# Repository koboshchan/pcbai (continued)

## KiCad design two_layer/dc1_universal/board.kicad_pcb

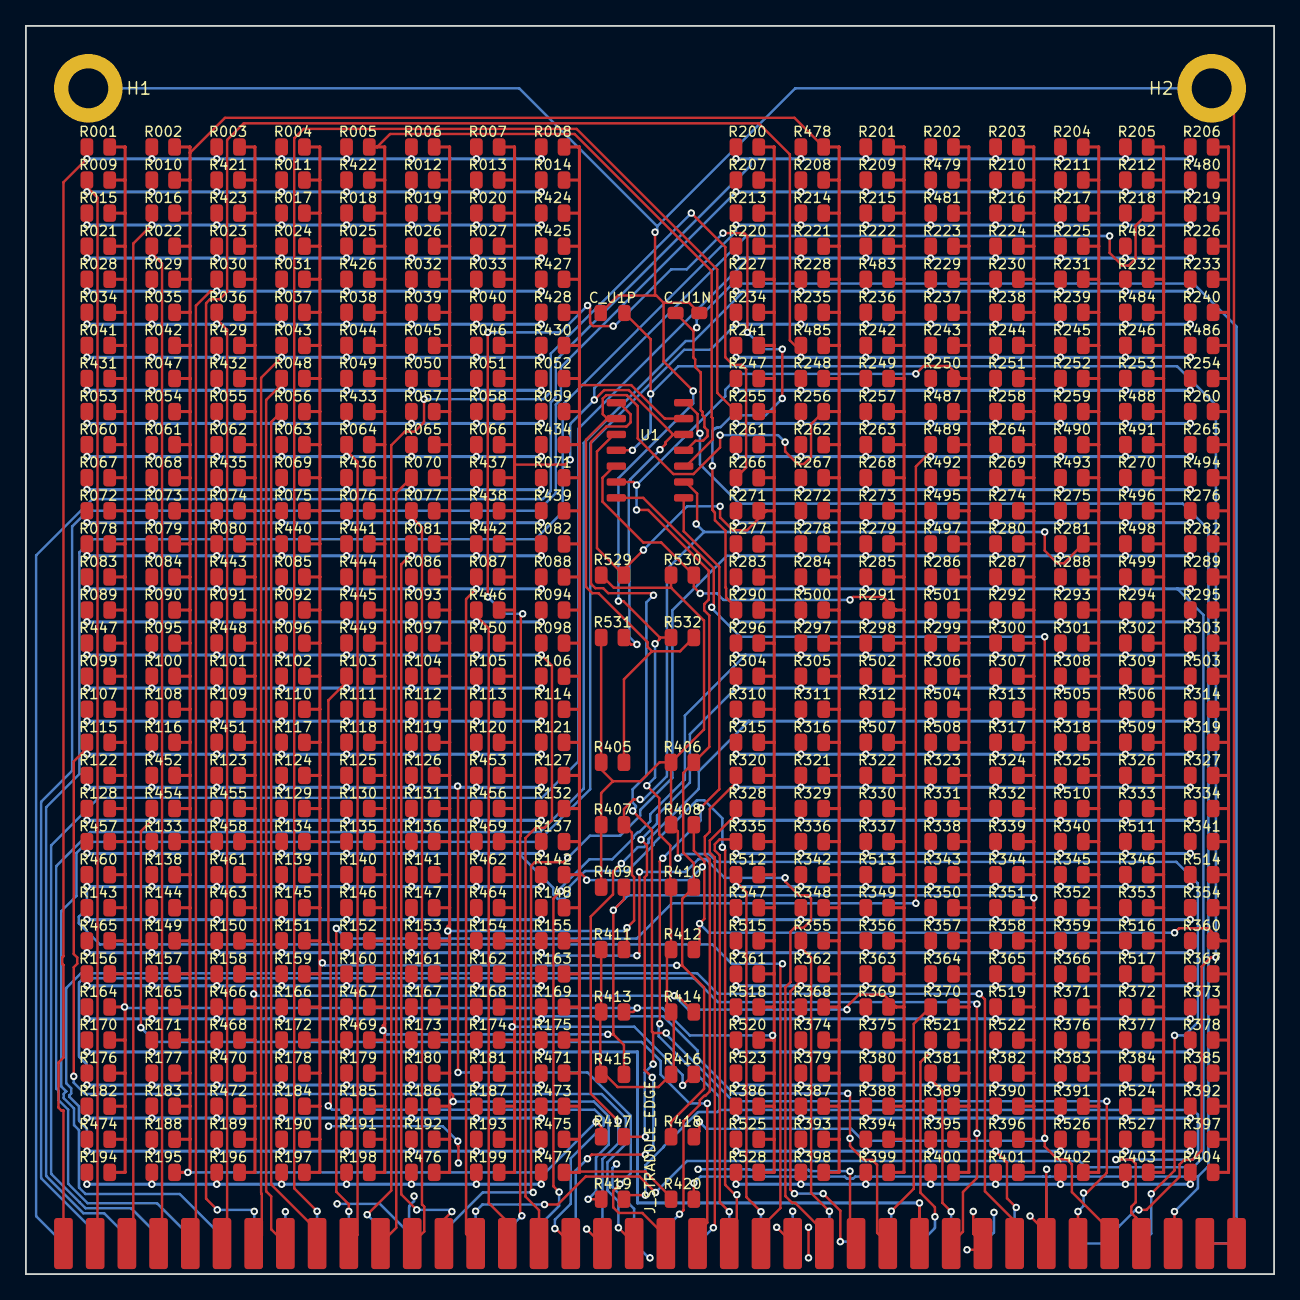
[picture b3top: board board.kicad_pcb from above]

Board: 4 copper layers, 100.0 x 100.0 mm, 538 parts (0 on the bottom side), 80 nets.

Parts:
C_U1N, C_U1P: 0.1uF; C_0805_2012Metric
H1, H2: MountingHole; MountingHole_3.2mm_M3_Pad
J_STRADDLE_EDGE: PinHeader_2x38_Straddle; PinHeader_2x38_Straddle_P2.54mm
R001, R002, R003, R004, R005, R006, R007, R008, R009, R010, R011, R012, R013, R014, R015, R016, R017, R018, R019, R020, R021, R022, R023, R024, R025, R026, R027, R028, R029, R030, R031, R032, R033, R034, R035, R036, R037, R038, R039, R040, R041, R042, R043, R044, R045, R046, R047, R048, R049, R050, R051, R052, R053, R054, R055, R056, R057, R058, R059, R060, R061, R062, R063, R064, R065, R066, R067, R068, R069, R070, R071, R072, R073, R074, R075, R076, R077, R078, R079, R080, R081, R082, R083, R084, R085, R086, R087, R088, R089, R090, R091, R092, R093, R094, R095, R096, R097, R098, R099, R100, R101, R102, R103, R104, R105, R106, R107, R108, R109, R110, R111, R112, R113, R114, R115, R116, R117, R118, R119, R120, R121, R122, R123, R124, R125, R126, R127, R128, R129, R130, R131, R132, R133, R134, R135, R136, R137, R138, R139, R140, R141, R142, R143, R144, R145, R146, R147, R148, R149, R150, R151, R152, R153, R154, R155, R156, R157, R158, R159, R160, R161, R162, R163, R164, R165, R166, R167, R168, R169, R170, R171, R172, R173, R174, R175, R176, R177, R178, R179, R180, R181, R182, R183, R184, R185, R186, R187, R188, R189, R190, R191, R192, R193, R194, R195, R196, R197, R198, R199, R200, R201, R202, R203, R204, R205, R206, R207, R208, R209, R210, R211, R212, R213, R214, R215, R216, R217, R218, R219, R220, R221, R222, R223, R224, R225, R226, R227, R228, R229, R230, R231, R232, R233, R234, R235, R236, R237, R238, R239, R240, R241, R242, R243, R244, R245, R246, R247, R248, R249, R250, R251, R252, R253, R254, R255, R256, R257, R258, R259, R260, R261, R262, R263, R264, R265, R266, R267, R268, R269, R270, R271, R272, R273, R274, R275, R276, R277, R278, R279, R280, R281, R282, R283, R284, R285, R286, R287, R288, R289, R290, R291, R292, R293, R294, R295, R296, R297, R298, R299, R300, R301, R302, R303, R304, R305, R306, R307, R308, R309, R310, R311, R312, R313, R314, R315, R316, R317, R318, R319, R320, R321, R322, R323, R324, R325, R326, R327, R328, R329, R330, R331, R332, R333, R334, R335, R336, R337, R338, R339, R340, R341, R342, R343, R344, R345, R346, R347, R348, R349, R350, R351, R352, R353, R354, R355, R356, R357, R358, R359, R360, R361, R362, R363, R364, R365, R366, R367, R368, R369, R370, R371, R372, R373, R374, R375, R376, R377, R378, R379, R380, R381, R382, R383, R384, R385, R386, R387, R388, R389, R390, R391, R392, R393, R394, R395, R396, R397, R398, R399, R400, R401, R402, R403, R404, R405, R406, R407, R408, R409, R410, R411, R412, R413, R414, R415, R416, R417, R418, R419, R420, R421, R422, R423, R424, R425, R426, R427, R428, R429, R430, R431, R432, R433, R434, R435, R436, R437, R438, R439, R440, R441, R442, R443, R444, R445, R446, R447, R448, R449, R450, R451, R452, R453, R454, R455, R456, R457, R458, R459, R460, R461, R462, R463, R464, R465, R466, R467, R468, R469, R470, R471, R472, R473, R474, R475, R476, R477, R478, R479, R480, R481, R482, R483, R484, R485, R486, R487, R488, R489, R490, R491, R492, R493, R494, R495, R496, R497, R498, R499, R500, R501, R502, R503, R504, R505, R506, R507, R508, R509, R510, R511, R512, R513, R514, R515, R516, R517, R518, R519, R520, R521, R522, R523, R524, R525, R526, R527, R528, R529, R530, R531, R532: POPULATION; R_0805_2012Metric
U1: TL074; SOIC-14_3.9x8.7mm_P1.27mm

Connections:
+5V_REF: J_STRADDLE_EDGE.B35, R405.1, R406.1, R407.1, R408.1, R409.1, R529.1, R530.1, R531.1
+15V: C_U1P.2, J_STRADDLE_EDGE.B33, J_STRADDLE_EDGE.B34, U1.4
-15V: C_U1N.1, J_STRADDLE_EDGE.B37, J_STRADDLE_EDGE.B38, U1.11
GND: C_U1N.2, C_U1P.1, H1.1, H2.1, J_STRADDLE_EDGE.A37, J_STRADDLE_EDGE.A38, R410.1, R411.1, R412.1, R413.1, R414.1, R415.1, R416.1, R532.1
INV_N0: R002.2, R010.2, R016.2, R022.2, R029.2, R035.2, R042.2, R047.2, R054.2, R061.2, R068.2, R073.2, R079.2, R084.2, R090.2, R095.2, R100.2, R108.2, R116.2, R133.2, R138.2, R144.2, R149.2, R157.2, R165.2, R171.2, R177.2, R183.2, R188.2, R195.2, R208.2, R214.2, R221.2, R228.2, R235.2, R248.2, R256.2, R262.2, R267.2, R272.2, R278.2, R284.2, R297.2, R305.2, R311.2, R316.2, R321.2, R329.2, R336.2, R342.2, R348.2, R355.2, R362.2, R368.2, R374.2, R379.2, R387.2, R393.2, R398.2, R405.2, R417.1, R452.2, R454.2, R478.2, R485.2, R500.2, R532.2, U1.2
INV_N1: R004.2, R011.2, R017.2, R024.2, R031.2, R037.2, R043.2, R048.2, R056.2, R063.2, R069.2, R075.2, R085.2, R092.2, R096.2, R102.2, R110.2, R117.2, R124.2, R129.2, R134.2, R139.2, R145.2, R151.2, R159.2, R166.2, R172.2, R178.2, R184.2, R190.2, R197.2, R202.2, R223.2, R229.2, R237.2, R243.2, R250.2, R286.2, R299.2, R306.2, R323.2, R331.2, R338.2, R343.2, R350.2, R357.2, R364.2, R370.2, R381.2, R389.2, R395.2, R400.2, R406.2, R410.2, R418.1, R440.2, R479.2, R481.2, R487.2, R489.2, R492.2, R495.2, R497.2, R501.2, R504.2, R508.2, R521.2, U1.6
INV_N2: R006.2, R012.2, R019.2, R026.2, R032.2, R039.2, R045.2, R050.2, R057.2, R065.2, R070.2, R077.2, R081.2, R086.2, R093.2, R097.2, R104.2, R112.2, R119.2, R126.2, R131.2, R136.2, R141.2, R147.2, R153.2, R161.2, R167.2, R173.2, R180.2, R186.2, R192.2, R204.2, R211.2, R217.2, R225.2, R231.2, R239.2, R245.2, R252.2, R259.2, R275.2, R281.2, R288.2, R293.2, R301.2, R308.2, R318.2, R325.2, R340.2, R345.2, R352.2, R359.2, R366.2, R371.2, R376.2, R383.2, R391.2, R402.2, R407.2, R411.2, R419.1, R476.2, R490.2, R493.2, R505.2, R510.2, R526.2, U1.9
INV_N3: R008.2, R014.2, R052.2, R059.2, R071.2, R082.2, R088.2, R094.2, R098.2, R106.2, R114.2, R121.2, R127.2, R132.2, R137.2, R142.2, R148.2, R155.2, R163.2, R169.2, R175.2, R206.2, R219.2, R226.2, R233.2, R240.2, R254.2, R260.2, R265.2, R276.2, R282.2, R289.2, R295.2, R303.2, R314.2, R319.2, R327.2, R334.2, R341.2, R354.2, R360.2, R367.2, R373.2, R378.2, R385.2, R392.2, R397.2, R404.2, R408.2, R412.2, R420.1, R424.2, R425.2, R427.2, R428.2, R430.2, R434.2, R439.2, R471.2, R473.2, R475.2, R477.2, R480.2, R486.2, R494.2, R503.2, R514.2, U1.13
IN_0: J_STRADDLE_EDGE.A1, R001.1, R002.1, R003.1, R004.1, R005.1, R006.1, R007.1, R008.1
IN_1: J_STRADDLE_EDGE.A2, R009.1, R010.1, R011.1, R012.1, R013.1, R014.1, R421.1, R422.1
IN_2: J_STRADDLE_EDGE.A3, R015.1, R016.1, R017.1, R018.1, R019.1, R020.1, R423.1, R424.1
IN_3: J_STRADDLE_EDGE.A4, R021.1, R022.1, R023.1, R024.1, R025.1, R026.1, R027.1, R425.1
IN_4: J_STRADDLE_EDGE.A5, R028.1, R029.1, R030.1, R031.1, R032.1, R033.1, R426.1, R427.1
IN_5: J_STRADDLE_EDGE.A6, R034.1, R035.1, R036.1, R037.1, R038.1, R039.1, R040.1, R428.1
IN_6: J_STRADDLE_EDGE.A7, R041.1, R042.1, R043.1, R044.1, R045.1, R046.1, R429.1, R430.1
IN_7: J_STRADDLE_EDGE.A8, R047.1, R048.1, R049.1, R050.1, R051.1, R052.1, R431.1, R432.1
IN_8: J_STRADDLE_EDGE.A9, R053.1, R054.1, R055.1, R056.1, R057.1, R058.1, R059.1, R433.1
IN_9: J_STRADDLE_EDGE.A10, R060.1, R061.1, R062.1, R063.1, R064.1, R065.1, R066.1, R434.1
IN_10: J_STRADDLE_EDGE.A11, R067.1, R068.1, R069.1, R070.1, R071.1, R435.1, R436.1, R437.1
IN_11: J_STRADDLE_EDGE.A12, R072.1, R073.1, R074.1, R075.1, R076.1, R077.1, R438.1, R439.1
IN_12: J_STRADDLE_EDGE.A13, R078.1, R079.1, R080.1, R081.1, R082.1, R440.1, R441.1, R442.1
IN_13: J_STRADDLE_EDGE.A14, R083.1, R084.1, R085.1, R086.1, R087.1, R088.1, R443.1, R444.1
IN_14: J_STRADDLE_EDGE.A15, R089.1, R090.1, R091.1, R092.1, R093.1, R094.1, R445.1, R446.1
IN_15: J_STRADDLE_EDGE.A16, R095.1, R096.1, R097.1, R098.1, R447.1, R448.1, R449.1, R450.1
IN_16: J_STRADDLE_EDGE.A17, R099.1, R100.1, R101.1, R102.1, R103.1, R104.1, R105.1, R106.1
IN_17: J_STRADDLE_EDGE.A18, R107.1, R108.1, R109.1, R110.1, R111.1, R112.1, R113.1, R114.1
IN_18: J_STRADDLE_EDGE.A19, R115.1, R116.1, R117.1, R118.1, R119.1, R120.1, R121.1, R451.1
IN_19: J_STRADDLE_EDGE.A20, R122.1, R123.1, R124.1, R125.1, R126.1, R127.1, R452.1, R453.1
IN_20: J_STRADDLE_EDGE.A21, R128.1, R129.1, R130.1, R131.1, R132.1, R454.1, R455.1, R456.1
IN_21: J_STRADDLE_EDGE.A22, R133.1, R134.1, R135.1, R136.1, R137.1, R457.1, R458.1, R459.1
IN_22: J_STRADDLE_EDGE.A23, R138.1, R139.1, R140.1, R141.1, R142.1, R460.1, R461.1, R462.1
IN_23: J_STRADDLE_EDGE.A24, R143.1, R144.1, R145.1, R146.1, R147.1, R148.1, R463.1, R464.1
IN_24: J_STRADDLE_EDGE.A25, R149.1, R150.1, R151.1, R152.1, R153.1, R154.1, R155.1, R465.1
IN_25: J_STRADDLE_EDGE.A26, R156.1, R157.1, R158.1, R159.1, R160.1, R161.1, R162.1, R163.1
IN_26: J_STRADDLE_EDGE.A27, R164.1, R165.1, R166.1, R167.1, R168.1, R169.1, R466.1, R467.1
IN_27: J_STRADDLE_EDGE.A28, R170.1, R171.1, R172.1, R173.1, R174.1, R175.1, R468.1, R469.1
IN_28: J_STRADDLE_EDGE.A29, R176.1, R177.1, R178.1, R179.1, R180.1, R181.1, R470.1, R471.1
IN_29: J_STRADDLE_EDGE.A30, R182.1, R183.1, R184.1, R185.1, R186.1, R187.1, R472.1, R473.1
IN_30: J_STRADDLE_EDGE.A31, R188.1, R189.1, R190.1, R191.1, R192.1, R193.1, R474.1, R475.1
IN_31: J_STRADDLE_EDGE.A32, R194.1, R195.1, R196.1, R197.1, R198.1, R199.1, R476.1, R477.1
IN_32: J_STRADDLE_EDGE.B1, R200.1, R201.1, R202.1, R203.1, R204.1, R205.1, R206.1, R478.1
IN_33: J_STRADDLE_EDGE.B2, R207.1, R208.1, R209.1, R210.1, R211.1, R212.1, R479.1, R480.1
IN_34: J_STRADDLE_EDGE.B3, R213.1, R214.1, R215.1, R216.1, R217.1, R218.1, R219.1, R481.1
IN_35: J_STRADDLE_EDGE.B4, R220.1, R221.1, R222.1, R223.1, R224.1, R225.1, R226.1, R482.1
IN_36: J_STRADDLE_EDGE.B5, R227.1, R228.1, R229.1, R230.1, R231.1, R232.1, R233.1, R483.1
IN_37: J_STRADDLE_EDGE.B6, R234.1, R235.1, R236.1, R237.1, R238.1, R239.1, R240.1, R484.1
IN_38: J_STRADDLE_EDGE.B7, R241.1, R242.1, R243.1, R244.1, R245.1, R246.1, R485.1, R486.1
IN_39: J_STRADDLE_EDGE.B8, R247.1, R248.1, R249.1, R250.1, R251.1, R252.1, R253.1, R254.1
IN_40: J_STRADDLE_EDGE.B9, R255.1, R256.1, R257.1, R258.1, R259.1, R260.1, R487.1, R488.1
IN_41: J_STRADDLE_EDGE.B10, R261.1, R262.1, R263.1, R264.1, R265.1, R489.1, R490.1, R491.1
IN_42: J_STRADDLE_EDGE.B11, R266.1, R267.1, R268.1, R269.1, R270.1, R492.1, R493.1, R494.1
IN_43: J_STRADDLE_EDGE.B12, R271.1, R272.1, R273.1, R274.1, R275.1, R276.1, R495.1, R496.1
IN_44: J_STRADDLE_EDGE.B13, R277.1, R278.1, R279.1, R280.1, R281.1, R282.1, R497.1, R498.1
IN_45: J_STRADDLE_EDGE.B14, R283.1, R284.1, R285.1, R286.1, R287.1, R288.1, R289.1, R499.1
IN_46: J_STRADDLE_EDGE.B15, R290.1, R291.1, R292.1, R293.1, R294.1, R295.1, R500.1, R501.1
IN_47: J_STRADDLE_EDGE.B16, R296.1, R297.1, R298.1, R299.1, R300.1, R301.1, R302.1, R303.1
IN_48: J_STRADDLE_EDGE.B17, R304.1, R305.1, R306.1, R307.1, R308.1, R309.1, R502.1, R503.1
IN_49: J_STRADDLE_EDGE.B18, R310.1, R311.1, R312.1, R313.1, R314.1, R504.1, R505.1, R506.1
IN_50: J_STRADDLE_EDGE.B19, R315.1, R316.1, R317.1, R318.1, R319.1, R507.1, R508.1, R509.1
IN_51: J_STRADDLE_EDGE.B20, R320.1, R321.1, R322.1, R323.1, R324.1, R325.1, R326.1, R327.1
IN_52: J_STRADDLE_EDGE.B21, R328.1, R329.1, R330.1, R331.1, R332.1, R333.1, R334.1, R510.1
IN_53: J_STRADDLE_EDGE.B22, R335.1, R336.1, R337.1, R338.1, R339.1, R340.1, R341.1, R511.1
IN_54: J_STRADDLE_EDGE.B23, R342.1, R343.1, R344.1, R345.1, R346.1, R512.1, R513.1, R514.1
IN_55: J_STRADDLE_EDGE.B24, R347.1, R348.1, R349.1, R350.1, R351.1, R352.1, R353.1, R354.1
IN_56: J_STRADDLE_EDGE.B25, R355.1, R356.1, R357.1, R358.1, R359.1, R360.1, R515.1, R516.1
IN_57: J_STRADDLE_EDGE.B26, R361.1, R362.1, R363.1, R364.1, R365.1, R366.1, R367.1, R517.1
IN_58: J_STRADDLE_EDGE.B27, R368.1, R369.1, R370.1, R371.1, R372.1, R373.1, R518.1, R519.1
IN_59: J_STRADDLE_EDGE.B28, R374.1, R375.1, R376.1, R377.1, R378.1, R520.1, R521.1, R522.1
IN_60: J_STRADDLE_EDGE.B29, R379.1, R380.1, R381.1, R382.1, R383.1, R384.1, R385.1, R523.1
IN_61: J_STRADDLE_EDGE.B30, R386.1, R387.1, R388.1, R389.1, R390.1, R391.1, R392.1, R524.1
IN_62: J_STRADDLE_EDGE.B31, R393.1, R394.1, R395.1, R396.1, R397.1, R525.1, R526.1, R527.1
IN_63: J_STRADDLE_EDGE.B32, R398.1, R399.1, R400.1, R401.1, R402.1, R403.1, R404.1, R528.1
POS_N0: R001.2, R009.2, R015.2, R021.2, R028.2, R034.2, R041.2, R053.2, R060.2, R067.2, R072.2, R078.2, R083.2, R089.2, R099.2, R107.2, R115.2, R122.2, R128.2, R143.2, R156.2, R164.2, R170.2, R176.2, R182.2, R194.2, R200.2, R207.2, R213.2, R220.2, R227.2, R234.2, R241.2, R247.2, R255.2, R261.2, R266.2, R271.2, R277.2, R283.2, R290.2, R296.2, R304.2, R310.2, R315.2, R320.2, R328.2, R335.2, R347.2, R361.2, R386.2, R413.2, R431.2, R447.2, R457.2, R460.2, R465.2, R474.2, R512.2, R515.2, R518.2, R520.2, R523.2, R525.2, R528.2, R529.2, U1.3
POS_N1: R003.2, R023.2, R030.2, R036.2, R055.2, R062.2, R074.2, R080.2, R091.2, R101.2, R109.2, R123.2, R150.2, R158.2, R189.2, R196.2, R201.2, R209.2, R215.2, R222.2, R236.2, R242.2, R249.2, R257.2, R263.2, R268.2, R273.2, R279.2, R285.2, R291.2, R298.2, R312.2, R322.2, R330.2, R337.2, R349.2, R356.2, R363.2, R369.2, R375.2, R380.2, R388.2, R394.2, R399.2, R414.2, R421.2, R423.2, R429.2, R432.2, R435.2, R443.2, R448.2, R451.2, R455.2, R458.2, R461.2, R463.2, R466.2, R468.2, R470.2, R472.2, R483.2, R502.2, R507.2, R513.2, R530.2, U1.5
POS_N2: R005.2, R018.2, R025.2, R038.2, R044.2, R049.2, R064.2, R076.2, R103.2, R111.2, R118.2, R125.2, R130.2, R135.2, R140.2, R146.2, R152.2, R160.2, R179.2, R185.2, R191.2, R198.2, R203.2, R210.2, R216.2, R224.2, R230.2, R238.2, R244.2, R251.2, R258.2, R264.2, R269.2, R274.2, R280.2, R287.2, R292.2, R300.2, R307.2, R313.2, R317.2, R324.2, R332.2, R339.2, R344.2, R351.2, R358.2, R365.2, R382.2, R390.2, R396.2, R401.2, R409.2, R415.2, R422.2, R426.2, R433.2, R436.2, R441.2, R444.2, R445.2, R449.2, R467.2, R469.2, R519.2, R522.2, U1.10
POS_N3: R007.2, R013.2, R020.2, R027.2, R033.2, R040.2, R046.2, R051.2, R058.2, R066.2, R087.2, R105.2, R113.2, R120.2, R154.2, R162.2, R168.2, R174.2, R181.2, R187.2, R193.2, R199.2, R205.2, R212.2, R218.2, R232.2, R246.2, R253.2, R270.2, R294.2, R302.2, R309.2, R326.2, R333.2, R346.2, R353.2, R372.2, R377.2, R384.2, R403.2, R416.2, R437.2, R438.2, R442.2, R446.2, R450.2, R453.2, R456.2, R459.2, R462.2, R464.2, R482.2, R484.2, R488.2, R491.2, R496.2, R498.2, R499.2, R506.2, R509.2, R511.2, R516.2, R517.2, R524.2, R527.2, R531.2, U1.12
V_SUM_0: J_STRADDLE_EDGE.A33, R417.2, U1.1
V_SUM_1: J_STRADDLE_EDGE.A34, R418.2, U1.7
V_SUM_2: J_STRADDLE_EDGE.A35, R419.2, U1.8
V_SUM_3: J_STRADDLE_EDGE.A36, R420.2, U1.14

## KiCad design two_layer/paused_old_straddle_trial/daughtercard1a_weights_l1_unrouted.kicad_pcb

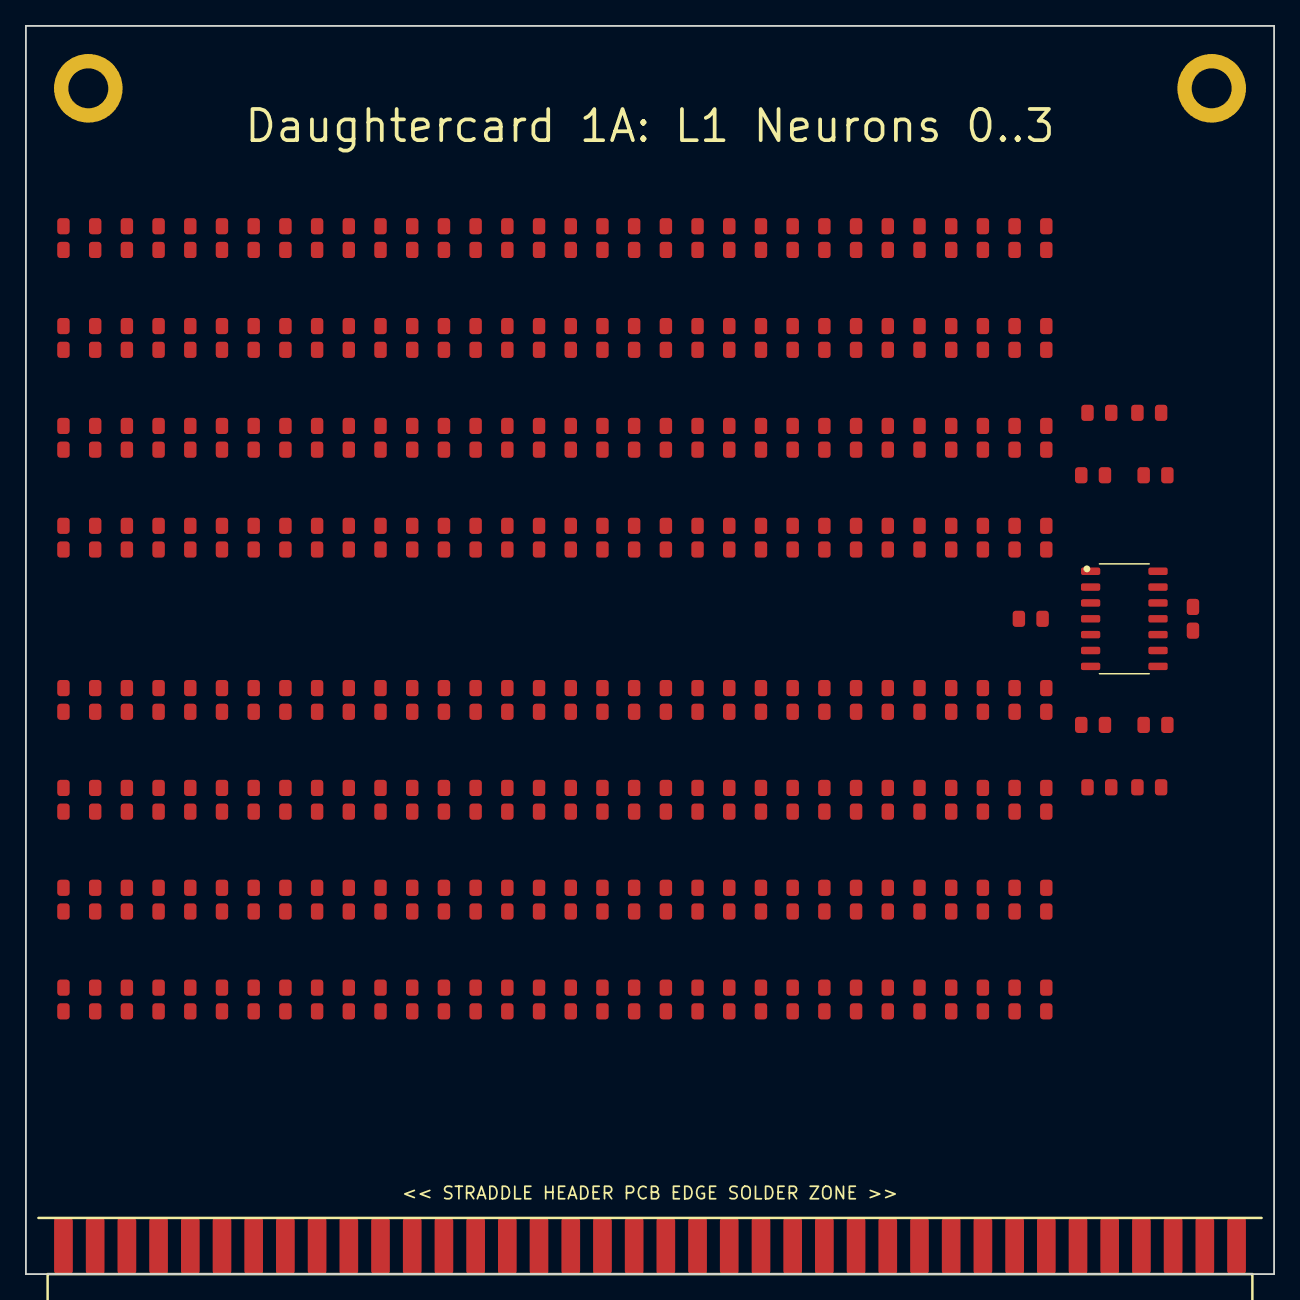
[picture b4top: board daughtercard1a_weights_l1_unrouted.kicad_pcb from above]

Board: 2 copper layers, 100.0 x 100.0 mm, 270 parts (0 on the bottom side), 77 nets, no tracks yet.

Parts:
C_U1N, C_U1P: 0.1uF; C_0805_2012Metric
H1, H2: MountingHole; MountingHole_3.2mm_M3_Pad
J_STRADDLE_EDGE: PinHeader_2x38_Straddle; PinHeader_2x38_Straddle_P2.54mm
R1_0_0: 3.3k; R_0805_2012Metric
R1_0_1, R1_6_1, R1_13_1, R1_14_1, R1_17_0, R1_25_1, R1_27_1, R1_46_0, R1_48_1: 300k; R_0805_2012Metric
R1_0_2, R1_2_2, R1_14_2, R1_21_3, R1_24_2, R1_29_3, R1_30_3, R1_33_0, R1_37_2, R1_38_3, R1_41_0, R1_43_0, R1_43_3, R1_49_2, R1_49_3, R1_51_2, R1_60_2, R1_60_3, R1_62_0: 43k; R_0805_2012Metric
R1_0_3, R1_16_3, R1_23_2, R1_47_0: 5.6k; R_0805_2012Metric
R1_1_0, R1_2_0, R1_3_3, R1_4_0, R1_18_2, R1_20_2, R1_24_0, R1_27_0, R1_41_3: 18k; R_0805_2012Metric
R1_1_1, R1_5_0, R1_26_1, R1_45_2, R1_47_1: 390k; R_0805_2012Metric
R1_1_2, R1_4_3, R1_5_2, R1_6_2, R1_8_0, R1_12_0, R1_19_3, R1_22_0, R1_31_3, R1_39_3, R1_47_3, R1_62_3: 15k; R_0805_2012Metric
R1_1_3, R1_3_2, R1_6_0, R1_8_3, R1_9_0, R1_9_3, R1_10_0, R1_14_0, R1_16_2, R1_23_3, R1_26_0, R1_26_2, R1_27_2, R1_29_0, R1_29_2, R1_30_2, R1_35_2, R1_36_2, R1_38_0, R1_42_0, R1_44_2, R1_46_2, R1_48_2, R1_49_0, R1_54_0, R1_54_2, R1_57_2: 33k; R_0805_2012Metric
R1_2_1, R1_3_1, R1_7_3, R1_9_1, R1_10_2, R1_11_2, R1_11_3, R1_12_3, R1_14_3, R1_15_1, R1_17_1, R1_20_3, R1_21_1, R1_23_1, R1_25_0, R1_32_1, R1_35_0, R1_36_1, R1_38_1, R1_38_2, R1_39_1, R1_41_1, R1_42_1, R1_43_1, R1_44_3, R1_48_0, R1_50_2, R1_52_2, R1_55_1, R1_58_1, R1_61_1, R1_63_0, R1_63_1: 100k; R_0805_2012Metric
R1_2_3, R1_21_0, R1_27_3, R1_39_2, R1_43_2, R1_55_0, R1_55_3, R1_56_3, R1_61_2: 12k; R_0805_2012Metric
R1_3_0, R1_5_3, R1_7_2, R1_9_2, R1_13_0, R1_15_0, R1_17_2, R1_19_2, R1_23_0, R1_28_0, R1_32_0, R1_33_2, R1_35_3, R1_59_2, R1_59_3, R1_61_0: 22k; R_0805_2012Metric
R1_4_1, R1_4_2, R1_5_1, R1_8_1, R1_8_2, R1_10_1, R1_10_3, R1_15_3, R1_18_0, R1_22_3, R1_31_0, R1_35_1, R1_44_0, R1_50_0, R1_51_0, R1_51_1, R1_51_3, R1_52_0, R1_53_3, R1_54_1, R1_54_3, R1_55_2, R1_57_1, R1_57_3: 75k; R_0805_2012Metric
R1_6_3, R1_32_2, R1_34_2, R1_42_2, R1_47_2, R1_48_3: 20k; R_0805_2012Metric
R1_7_0, R1_15_2, R1_36_0, R1_40_0: 47k; R_0805_2012Metric
R1_7_1, R1_11_0, R1_16_0, R1_16_1, R1_18_1, R1_19_1, R1_20_0, R1_24_1, R1_25_2, R1_28_2, R1_31_1, R1_33_1, R1_34_0, R1_34_1, R1_37_1, R1_40_2, R1_41_2, R1_42_3, R1_45_0, R1_45_3, R1_46_1, R1_46_3, R1_52_1, R1_52_3, R1_53_0, R1_57_0, R1_58_3, R1_62_1: 200k; R_0805_2012Metric
R1_11_1, R1_12_1, R1_13_2, R1_28_3, R1_30_0, R1_30_1, R1_34_3, R1_44_1, R1_45_1, R1_49_1, R1_50_1, R1_50_3, R1_53_1, R1_53_2, R1_56_2, R1_58_2, R1_59_0, R1_59_1, R1_60_1, R1_61_3: 51k; R_0805_2012Metric
R1_12_2, R1_20_1, R1_22_1, R1_28_1, R1_29_1, R1_40_1, R1_60_0: 1M; R_0805_2012Metric
R1_13_3, R1_36_3: 470k; R_0805_2012Metric
R1_17_3, R1_24_3, R1_25_3, R1_56_0, R1_63_3: 7.5k; R_0805_2012Metric
R1_18_3, R1_19_0, R1_21_2, R1_22_2, R1_26_3, R1_31_2, R1_33_3, R1_39_0, R1_62_2: 10k; R_0805_2012Metric
R1_32_3: 3k; R_0805_2012Metric
R1_37_0, R1_37_3: 680k; R_0805_2012Metric
R1_40_3: 5.1k; R_0805_2012Metric
R1_56_1: DNP; R_0805_2012Metric
R1_58_0: 10M; R_0805_2012Metric
R1_63_2: 4.7k; R_0805_2012Metric
Rb_N0, Rb_N3: 200k; R_0805_2012Metric
Rb_N1: 470k; R_0805_2012Metric
Rb_N2: 100k; R_0805_2012Metric
Rf_N0, Rf_N1, Rf_N2, Rf_N3: 10k; R_0805_2012Metric
U1: TL074; SOIC-14_3.9x8.7mm_P1.27mm

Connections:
+5V_REF: J_STRADDLE_EDGE.B35, Rb_N1.2
+12V: C_U1P.2, J_STRADDLE_EDGE.B33, J_STRADDLE_EDGE.B34, U1.4
-5V_REF: J_STRADDLE_EDGE.B36, Rb_N0.2, Rb_N2.1, Rb_N3.1
-12V: C_U1N.1, J_STRADDLE_EDGE.B37, J_STRADDLE_EDGE.B38, U1.11
GND: C_U1N.2, C_U1P.1, H1.1, H2.1, J_STRADDLE_EDGE.A37, J_STRADDLE_EDGE.A38, U1.3, U1.5, U1.10, U1.12
INV_N0: R1_0_0.2, R1_1_0.2, R1_2_0.2, R1_3_0.2, R1_4_0.2, R1_5_0.2, R1_6_0.2, R1_7_0.2, R1_8_0.2, R1_9_0.2, R1_10_0.2, R1_11_0.2, R1_12_0.2, R1_13_0.2, R1_14_0.2, R1_15_0.2, R1_16_0.2, R1_17_0.2, R1_18_0.2, R1_19_0.2, R1_20_0.2, R1_21_0.2, R1_22_0.2, R1_23_0.2, R1_24_0.2, R1_25_0.2, R1_26_0.2, R1_27_0.2, R1_28_0.2, R1_29_0.2, R1_30_0.2, R1_31_0.2, R1_32_0.2, R1_33_0.2, R1_34_0.2, R1_35_0.2, R1_36_0.2, R1_37_0.2, R1_38_0.2, R1_39_0.2, R1_40_0.2, R1_41_0.2, R1_42_0.2, R1_43_0.2, R1_44_0.2, R1_45_0.2, R1_46_0.2, R1_47_0.2, R1_48_0.2, R1_49_0.2, R1_50_0.2, R1_51_0.2, R1_52_0.2, R1_53_0.2, R1_54_0.2, R1_55_0.2, R1_56_0.2, R1_57_0.2, R1_58_0.2, R1_59_0.2, R1_60_0.2, R1_61_0.2, R1_62_0.2, R1_63_0.2, Rb_N0.1, Rf_N0.2, U1.2
INV_N1: R1_0_1.2, R1_1_1.2, R1_2_1.2, R1_3_1.2, R1_4_1.2, R1_5_1.2, R1_6_1.2, R1_7_1.2, R1_8_1.2, R1_9_1.2, R1_10_1.2, R1_11_1.2, R1_12_1.2, R1_13_1.2, R1_14_1.2, R1_15_1.2, R1_16_1.2, R1_17_1.2, R1_18_1.2, R1_19_1.2, R1_20_1.2, R1_21_1.2, R1_22_1.2, R1_23_1.2, R1_24_1.2, R1_25_1.2, R1_26_1.2, R1_27_1.2, R1_28_1.2, R1_29_1.2, R1_30_1.2, R1_31_1.2, R1_32_1.2, R1_33_1.2, R1_34_1.2, R1_35_1.2, R1_36_1.2, R1_37_1.2, R1_38_1.2, R1_39_1.2, R1_40_1.2, R1_41_1.2, R1_42_1.2, R1_43_1.2, R1_44_1.2, R1_45_1.2, R1_46_1.2, R1_47_1.2, R1_48_1.2, R1_49_1.2, R1_50_1.2, R1_51_1.2, R1_52_1.2, R1_53_1.2, R1_54_1.2, R1_55_1.2, R1_56_1.2, R1_57_1.2, R1_58_1.2, R1_59_1.2, R1_60_1.2, R1_61_1.2, R1_62_1.2, R1_63_1.2, Rb_N1.1, Rf_N1.2, U1.6
INV_N2: R1_0_2.2, R1_1_2.2, R1_2_2.2, R1_3_2.2, R1_4_2.2, R1_5_2.2, R1_6_2.2, R1_7_2.2, R1_8_2.2, R1_9_2.2, R1_10_2.2, R1_11_2.2, R1_12_2.2, R1_13_2.2, R1_14_2.2, R1_15_2.2, R1_16_2.2, R1_17_2.2, R1_18_2.2, R1_19_2.2, R1_20_2.2, R1_21_2.2, R1_22_2.2, R1_23_2.2, R1_24_2.2, R1_25_2.2, R1_26_2.2, R1_27_2.2, R1_28_2.2, R1_29_2.2, R1_30_2.2, R1_31_2.2, R1_32_2.2, R1_33_2.2, R1_34_2.2, R1_35_2.2, R1_36_2.2, R1_37_2.2, R1_38_2.2, R1_39_2.2, R1_40_2.2, R1_41_2.2, R1_42_2.2, R1_43_2.2, R1_44_2.2, R1_45_2.2, R1_46_2.2, R1_47_2.2, R1_48_2.2, R1_49_2.2, R1_50_2.2, R1_51_2.2, R1_52_2.2, R1_53_2.2, R1_54_2.2, R1_55_2.2, R1_56_2.2, R1_57_2.2, R1_58_2.2, R1_59_2.2, R1_60_2.2, R1_61_2.2, R1_62_2.2, R1_63_2.2, Rb_N2.2, Rf_N2.1, U1.9
INV_N3: R1_0_3.2, R1_1_3.2, R1_2_3.2, R1_3_3.2, R1_4_3.2, R1_5_3.2, R1_6_3.2, R1_7_3.2, R1_8_3.2, R1_9_3.2, R1_10_3.2, R1_11_3.2, R1_12_3.2, R1_13_3.2, R1_14_3.2, R1_15_3.2, R1_16_3.2, R1_17_3.2, R1_18_3.2, R1_19_3.2, R1_20_3.2, R1_21_3.2, R1_22_3.2, R1_23_3.2, R1_24_3.2, R1_25_3.2, R1_26_3.2, R1_27_3.2, R1_28_3.2, R1_29_3.2, R1_30_3.2, R1_31_3.2, R1_32_3.2, R1_33_3.2, R1_34_3.2, R1_35_3.2, R1_36_3.2, R1_37_3.2, R1_38_3.2, R1_39_3.2, R1_40_3.2, R1_41_3.2, R1_42_3.2, R1_43_3.2, R1_44_3.2, R1_45_3.2, R1_46_3.2, R1_47_3.2, R1_48_3.2, R1_49_3.2, R1_50_3.2, R1_51_3.2, R1_52_3.2, R1_53_3.2, R1_54_3.2, R1_55_3.2, R1_56_3.2, R1_57_3.2, R1_58_3.2, R1_59_3.2, R1_60_3.2, R1_61_3.2, R1_62_3.2, R1_63_3.2, Rb_N3.2, Rf_N3.1, U1.13
IN_0: J_STRADDLE_EDGE.A1, R1_0_0.1, R1_0_1.1, R1_0_2.1, R1_0_3.1
IN_1: J_STRADDLE_EDGE.A2, R1_1_0.1, R1_1_1.1, R1_1_2.1, R1_1_3.1
IN_2: J_STRADDLE_EDGE.A3, R1_2_0.1, R1_2_1.1, R1_2_2.1, R1_2_3.1
IN_3: J_STRADDLE_EDGE.A4, R1_3_0.1, R1_3_1.1, R1_3_2.1, R1_3_3.1
IN_4: J_STRADDLE_EDGE.A5, R1_4_0.1, R1_4_1.1, R1_4_2.1, R1_4_3.1
IN_5: J_STRADDLE_EDGE.A6, R1_5_0.1, R1_5_1.1, R1_5_2.1, R1_5_3.1
IN_6: J_STRADDLE_EDGE.A7, R1_6_0.1, R1_6_1.1, R1_6_2.1, R1_6_3.1
IN_7: J_STRADDLE_EDGE.A8, R1_7_0.1, R1_7_1.1, R1_7_2.1, R1_7_3.1
IN_8: J_STRADDLE_EDGE.A9, R1_8_0.1, R1_8_1.1, R1_8_2.1, R1_8_3.1
IN_9: J_STRADDLE_EDGE.A10, R1_9_0.1, R1_9_1.1, R1_9_2.1, R1_9_3.1
IN_10: J_STRADDLE_EDGE.A11, R1_10_0.1, R1_10_1.1, R1_10_2.1, R1_10_3.1
IN_11: J_STRADDLE_EDGE.A12, R1_11_0.1, R1_11_1.1, R1_11_2.1, R1_11_3.1
IN_12: J_STRADDLE_EDGE.A13, R1_12_0.1, R1_12_1.1, R1_12_2.1, R1_12_3.1
IN_13: J_STRADDLE_EDGE.A14, R1_13_0.1, R1_13_1.1, R1_13_2.1, R1_13_3.1
IN_14: J_STRADDLE_EDGE.A15, R1_14_0.1, R1_14_1.1, R1_14_2.1, R1_14_3.1
IN_15: J_STRADDLE_EDGE.A16, R1_15_0.1, R1_15_1.1, R1_15_2.1, R1_15_3.1
IN_16: J_STRADDLE_EDGE.A17, R1_16_0.1, R1_16_1.1, R1_16_2.1, R1_16_3.1
IN_17: J_STRADDLE_EDGE.A18, R1_17_0.1, R1_17_1.1, R1_17_2.1, R1_17_3.1
IN_18: J_STRADDLE_EDGE.A19, R1_18_0.1, R1_18_1.1, R1_18_2.1, R1_18_3.1
IN_19: J_STRADDLE_EDGE.A20, R1_19_0.1, R1_19_1.1, R1_19_2.1, R1_19_3.1
IN_20: J_STRADDLE_EDGE.A21, R1_20_0.1, R1_20_1.1, R1_20_2.1, R1_20_3.1
IN_21: J_STRADDLE_EDGE.A22, R1_21_0.1, R1_21_1.1, R1_21_2.1, R1_21_3.1
IN_22: J_STRADDLE_EDGE.A23, R1_22_0.1, R1_22_1.1, R1_22_2.1, R1_22_3.1
IN_23: J_STRADDLE_EDGE.A24, R1_23_0.1, R1_23_1.1, R1_23_2.1, R1_23_3.1
IN_24: J_STRADDLE_EDGE.A25, R1_24_0.1, R1_24_1.1, R1_24_2.1, R1_24_3.1
IN_25: J_STRADDLE_EDGE.A26, R1_25_0.1, R1_25_1.1, R1_25_2.1, R1_25_3.1
IN_26: J_STRADDLE_EDGE.A27, R1_26_0.1, R1_26_1.1, R1_26_2.1, R1_26_3.1
IN_27: J_STRADDLE_EDGE.A28, R1_27_0.1, R1_27_1.1, R1_27_2.1, R1_27_3.1
IN_28: J_STRADDLE_EDGE.A29, R1_28_0.1, R1_28_1.1, R1_28_2.1, R1_28_3.1
IN_29: J_STRADDLE_EDGE.A30, R1_29_0.1, R1_29_1.1, R1_29_2.1, R1_29_3.1
IN_30: J_STRADDLE_EDGE.A31, R1_30_0.1, R1_30_1.1, R1_30_2.1, R1_30_3.1
IN_31: J_STRADDLE_EDGE.A32, R1_31_0.1, R1_31_1.1, R1_31_2.1, R1_31_3.1
IN_32: J_STRADDLE_EDGE.B1, R1_32_0.1, R1_32_1.1, R1_32_2.1, R1_32_3.1
IN_33: J_STRADDLE_EDGE.B2, R1_33_0.1, R1_33_1.1, R1_33_2.1, R1_33_3.1
IN_34: J_STRADDLE_EDGE.B3, R1_34_0.1, R1_34_1.1, R1_34_2.1, R1_34_3.1
IN_35: J_STRADDLE_EDGE.B4, R1_35_0.1, R1_35_1.1, R1_35_2.1, R1_35_3.1
IN_36: J_STRADDLE_EDGE.B5, R1_36_0.1, R1_36_1.1, R1_36_2.1, R1_36_3.1
IN_37: J_STRADDLE_EDGE.B6, R1_37_0.1, R1_37_1.1, R1_37_2.1, R1_37_3.1
IN_38: J_STRADDLE_EDGE.B7, R1_38_0.1, R1_38_1.1, R1_38_2.1, R1_38_3.1
IN_39: J_STRADDLE_EDGE.B8, R1_39_0.1, R1_39_1.1, R1_39_2.1, R1_39_3.1
IN_40: J_STRADDLE_EDGE.B9, R1_40_0.1, R1_40_1.1, R1_40_2.1, R1_40_3.1
IN_41: J_STRADDLE_EDGE.B10, R1_41_0.1, R1_41_1.1, R1_41_2.1, R1_41_3.1
IN_42: J_STRADDLE_EDGE.B11, R1_42_0.1, R1_42_1.1, R1_42_2.1, R1_42_3.1
IN_43: J_STRADDLE_EDGE.B12, R1_43_0.1, R1_43_1.1, R1_43_2.1, R1_43_3.1
IN_44: J_STRADDLE_EDGE.B13, R1_44_0.1, R1_44_1.1, R1_44_2.1, R1_44_3.1
IN_45: J_STRADDLE_EDGE.B14, R1_45_0.1, R1_45_1.1, R1_45_2.1, R1_45_3.1
IN_46: J_STRADDLE_EDGE.B15, R1_46_0.1, R1_46_1.1, R1_46_2.1, R1_46_3.1
IN_47: J_STRADDLE_EDGE.B16, R1_47_0.1, R1_47_1.1, R1_47_2.1, R1_47_3.1
IN_48: J_STRADDLE_EDGE.B17, R1_48_0.1, R1_48_1.1, R1_48_2.1, R1_48_3.1
IN_49: J_STRADDLE_EDGE.B18, R1_49_0.1, R1_49_1.1, R1_49_2.1, R1_49_3.1
IN_50: J_STRADDLE_EDGE.B19, R1_50_0.1, R1_50_1.1, R1_50_2.1, R1_50_3.1
IN_51: J_STRADDLE_EDGE.B20, R1_51_0.1, R1_51_1.1, R1_51_2.1, R1_51_3.1
IN_52: J_STRADDLE_EDGE.B21, R1_52_0.1, R1_52_1.1, R1_52_2.1, R1_52_3.1
IN_53: J_STRADDLE_EDGE.B22, R1_53_0.1, R1_53_1.1, R1_53_2.1, R1_53_3.1
IN_54: J_STRADDLE_EDGE.B23, R1_54_0.1, R1_54_1.1, R1_54_2.1, R1_54_3.1
IN_55: J_STRADDLE_EDGE.B24, R1_55_0.1, R1_55_1.1, R1_55_2.1, R1_55_3.1
IN_56: J_STRADDLE_EDGE.B25, R1_56_0.1, R1_56_1.1, R1_56_2.1, R1_56_3.1
IN_57: J_STRADDLE_EDGE.B26, R1_57_0.1, R1_57_1.1, R1_57_2.1, R1_57_3.1
IN_58: J_STRADDLE_EDGE.B27, R1_58_0.1, R1_58_1.1, R1_58_2.1, R1_58_3.1
IN_59: J_STRADDLE_EDGE.B28, R1_59_0.1, R1_59_1.1, R1_59_2.1, R1_59_3.1
IN_60: J_STRADDLE_EDGE.B29, R1_60_0.1, R1_60_1.1, R1_60_2.1, R1_60_3.1
IN_61: J_STRADDLE_EDGE.B30, R1_61_0.1, R1_61_1.1, R1_61_2.1, R1_61_3.1
IN_62: J_STRADDLE_EDGE.B31, R1_62_0.1, R1_62_1.1, R1_62_2.1, R1_62_3.1
IN_63: J_STRADDLE_EDGE.B32, R1_63_0.1, R1_63_1.1, R1_63_2.1, R1_63_3.1
V_SUM_0: J_STRADDLE_EDGE.A33, Rf_N0.1, U1.1
V_SUM_1: J_STRADDLE_EDGE.A34, Rf_N1.1, U1.7
V_SUM_2: J_STRADDLE_EDGE.A35, Rf_N2.2, U1.8
V_SUM_3: J_STRADDLE_EDGE.A36, Rf_N3.2, U1.14
